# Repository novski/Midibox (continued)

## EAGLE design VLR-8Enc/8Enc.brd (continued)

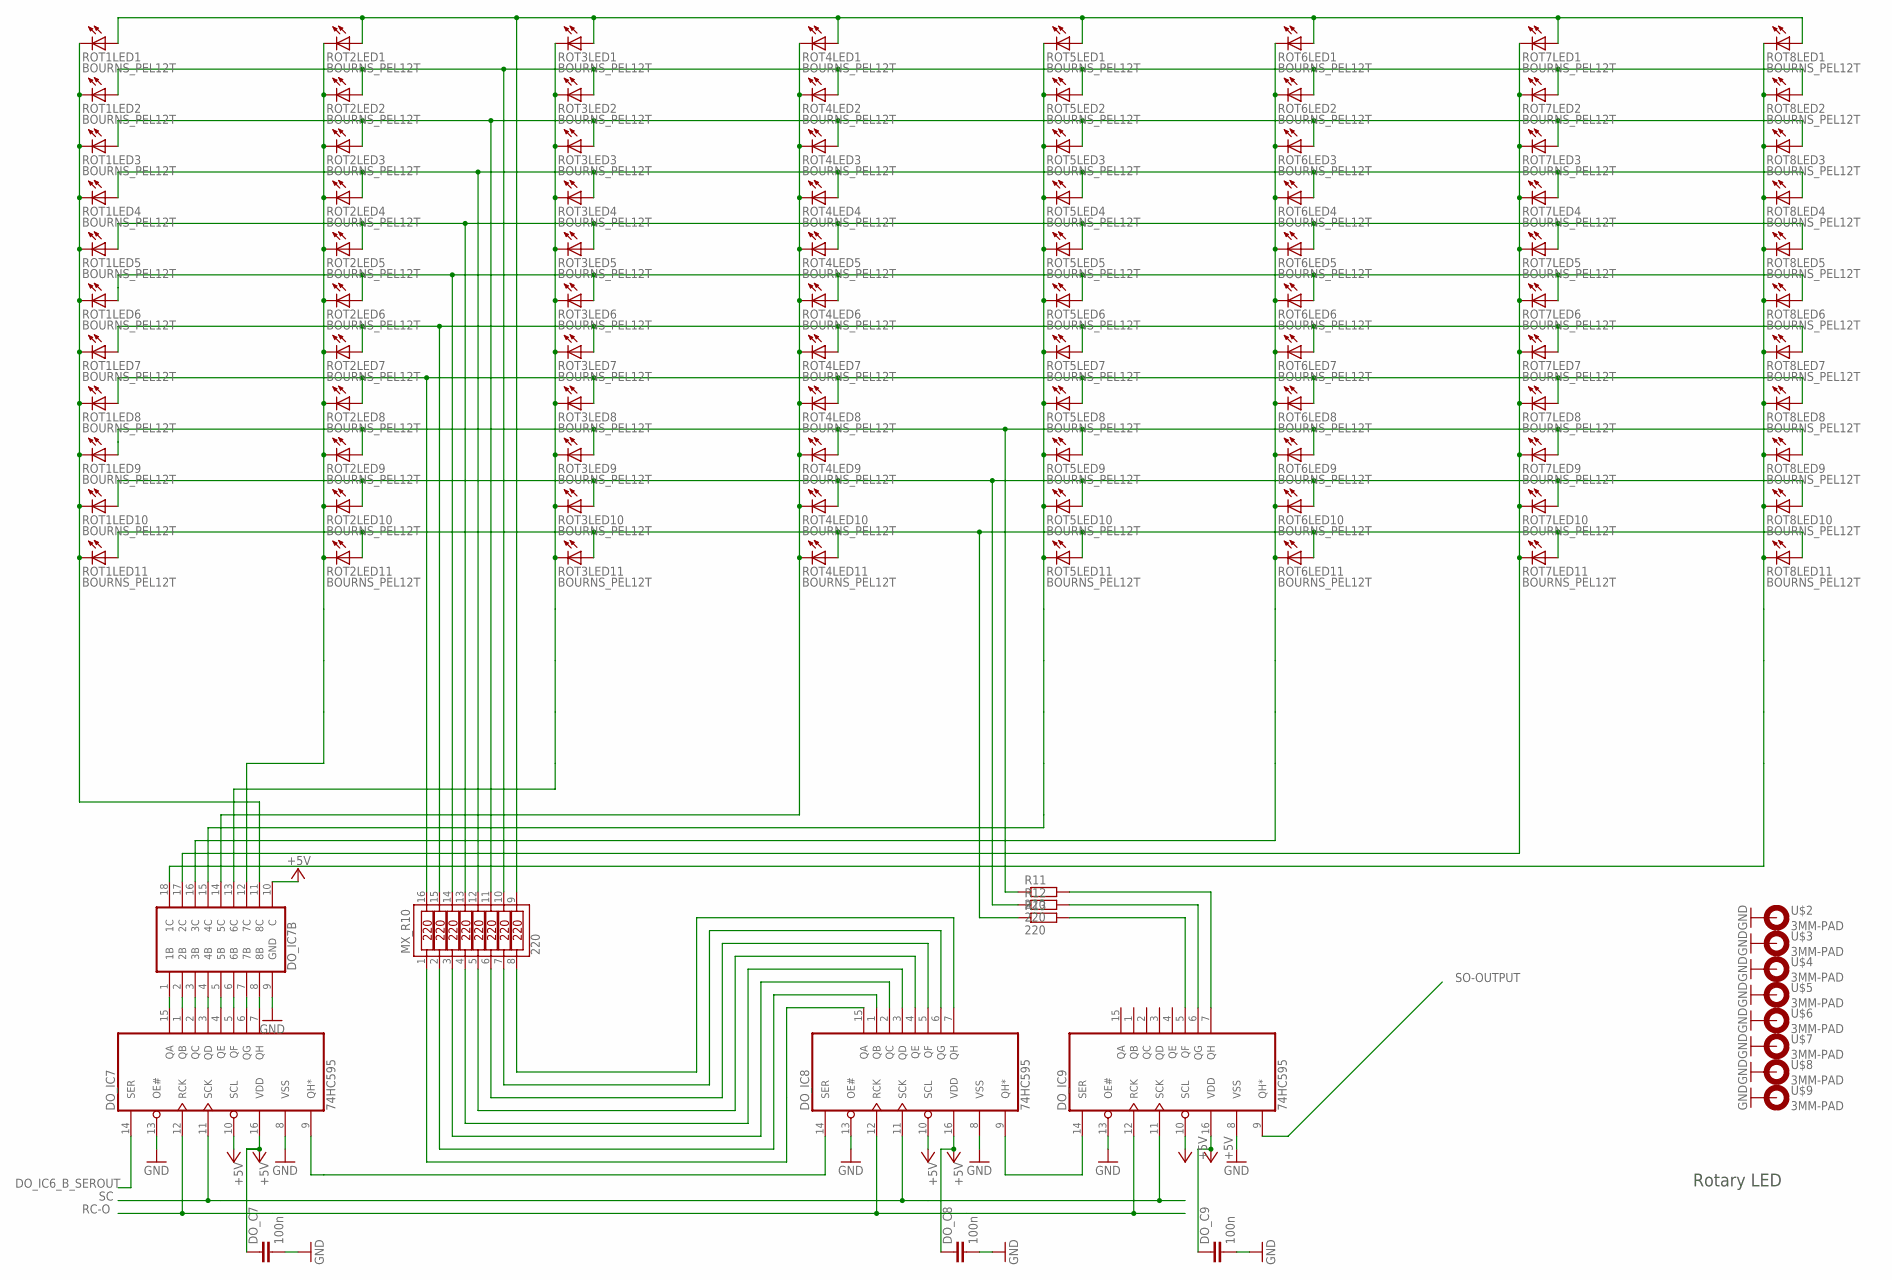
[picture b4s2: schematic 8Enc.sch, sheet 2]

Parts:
DO_C7, DO_C8, DO_C9: 100n; C025-024X044
DO_IC7, DO_IC8, DO_IC9: 74HC595; SO16D
DO_IC7B: ULN2803SO18W; SO18W
MX_R10: 220; SOIC16W
R11, R12, R13: 220; 0204/7
ROT1, ROT2, ROT3, ROT4, ROT5, ROT6, ROT7, ROT8: BOURNS_PEL12T; PEL12T_11-LED-RING
U$2, U$3, U$4, U$5, U$6, U$7, U$8, U$9: 3MM-PAD

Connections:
+5V: DO_C7.1, DO_C8.1, DO_C9.1, DO_IC7.10 (SCL), DO_IC7.16 (VDD), DO_IC7B.10 (C), DO_IC8.10 (SCL), DO_IC8.16 (VDD), DO_IC9.10 (SCL), DO_IC9.16 (VDD); also elsewhere on the board
DO_IC6_B_SEROUT: DO_IC7.14 (SER); also elsewhere on the board
DO_IC7_QA: DO_IC7.15 (QA), DO_IC7B.1 (1B)
DO_IC7_QB: DO_IC7.1 (QB), DO_IC7B.2 (2B)
DO_IC7_QC: DO_IC7.2 (QC), DO_IC7B.3 (3B)
DO_IC7_QD: DO_IC7.3 (QD), DO_IC7B.4 (4B)
DO_IC7_QE: DO_IC7.4 (QE), DO_IC7B.5 (5B)
DO_IC7_QF: DO_IC7.5 (QF), DO_IC7B.6 (6B)
DO_IC7_QG: DO_IC7.6 (QG), DO_IC7B.7 (7B)
DO_IC7_QH: DO_IC7.7 (QH), DO_IC7B.8 (8B)
DO_IC7_SEROUT: DO_IC7.9 (QH*), DO_IC8.14 (SER)
DO_IC8_QA: DO_IC8.15 (QA), MX_R10.1
DO_IC8_QB: DO_IC8.1 (QB), MX_R10.2
DO_IC8_QC: DO_IC8.2 (QC), MX_R10.3
DO_IC8_QD: DO_IC8.3 (QD), MX_R10.4
DO_IC8_QE: DO_IC8.4 (QE), MX_R10.5
DO_IC8_QF: DO_IC8.5 (QF), MX_R10.6
DO_IC8_QG: DO_IC8.6 (QG), MX_R10.7
DO_IC8_QH: DO_IC8.7 (QH), MX_R10.8
DO_IC8_SEROUT: DO_IC8.9 (QH*), DO_IC9.14 (SER)
DO_IC9_QF: DO_IC9.5 (QF), R13.2
DO_IC9_QG: DO_IC9.6 (QG), R12.2
DO_IC9_QH: DO_IC9.7 (QH), R11.2
GND: DO_C7.2, DO_C8.2, DO_C9.2, DO_IC7.8 (VSS), DO_IC7.13 (OE#), DO_IC7B.9 (GND), DO_IC8.8 (VSS), DO_IC8.13 (OE#), DO_IC9.8 (VSS), DO_IC9.13 (OE#), U$2.B3, U$3.B3, U$4.B3, U$5.B3, U$6.B3, U$7.B3, U$8.B3, U$9.B3; also elsewhere on the board
MATRIXLED1: MX_R10.9, ROT1.A1 (A), ROT2.A1 (A), ROT3.A1 (A), ROT4.A1 (A), ROT5.A1 (A), ROT6.A1 (A), ROT7.A1 (A), ROT8.A1 (A)
MATRIXLED2: MX_R10.10, ROT1.A2 (A), ROT2.A2 (A), ROT3.A2 (A), ROT4.A2 (A), ROT5.A2 (A), ROT6.A2 (A), ROT7.A2 (A), ROT8.A2 (A)
MATRIXLED3: MX_R10.11, ROT1.A3 (A), ROT2.A3 (A), ROT3.A3 (A), ROT4.A3 (A), ROT5.A3 (A), ROT6.A3 (A), ROT7.A3 (A), ROT8.A3 (A)
MATRIXLED4: MX_R10.12, ROT1.A4 (A), ROT2.A4 (A), ROT3.A4 (A), ROT4.A4 (A), ROT5.A4 (A), ROT6.A4 (A), ROT7.A4 (A), ROT8.A4 (A)
MATRIXLED5: MX_R10.13, ROT1.A5 (A), ROT2.A5 (A), ROT3.A5 (A), ROT4.A5 (A), ROT5.A5 (A), ROT6.A5 (A), ROT7.A5 (A), ROT8.A5 (A)
MATRIXLED6: MX_R10.14, ROT1.A6 (A), ROT2.A6 (A), ROT3.A6 (A), ROT4.A6 (A), ROT5.A6 (A), ROT6.A6 (A), ROT7.A6 (A), ROT8.A6 (A)
MATRIXLED7: MX_R10.15, ROT1.A7 (A), ROT2.A7 (A), ROT3.A7 (A), ROT4.A7 (A), ROT5.A7 (A), ROT6.A7 (A), ROT7.A7 (A), ROT8.A7 (A)
MATRIXLED8: MX_R10.16, ROT1.A8 (A), ROT2.A8 (A), ROT3.A8 (A), ROT4.A8 (A), ROT5.A8 (A), ROT6.A8 (A), ROT7.A8 (A), ROT8.A8 (A)
MATRIXLED9: R11.1, ROT1.A9 (A), ROT2.A9 (A), ROT3.A9 (A), ROT4.A9 (A), ROT5.A9 (A), ROT6.A9 (A), ROT7.A9 (A), ROT8.A9 (A)
MATRIXLED10: R12.1, ROT1.A10 (A), ROT2.A10 (A), ROT3.A10 (A), ROT4.A10 (A), ROT5.A10 (A), ROT6.A10 (A), ROT7.A10 (A), ROT8.A10 (A)
MATRIXLED11: R13.1, ROT1.A12 (A), ROT2.A12 (A), ROT3.A12 (A), ROT4.A12 (A), ROT5.A12 (A), ROT6.A12 (A), ROT7.A12 (A), ROT8.A12 (A)
MATRIXROT1: DO_IC7B.11 (8C), ROT1.K1 (C), ROT1.K2 (C), ROT1.K3 (C), ROT1.K4 (C), ROT1.K5 (C), ROT1.K6 (C), ROT1.K7 (C), ROT1.K8 (C), ROT1.K9 (C), ROT1.K10 (C), ROT1.K12 (C)
MATRIXROT2: DO_IC7B.12 (7C), ROT2.K1 (C), ROT2.K2 (C), ROT2.K3 (C), ROT2.K4 (C), ROT2.K5 (C), ROT2.K6 (C), ROT2.K7 (C), ROT2.K8 (C), ROT2.K9 (C), ROT2.K10 (C), ROT2.K12 (C)
MATRIXROT3: DO_IC7B.13 (6C), ROT3.K1 (C), ROT3.K2 (C), ROT3.K3 (C), ROT3.K4 (C), ROT3.K5 (C), ROT3.K6 (C), ROT3.K7 (C), ROT3.K8 (C), ROT3.K9 (C), ROT3.K10 (C), ROT3.K12 (C)
MATRIXROT4: DO_IC7B.14 (5C), ROT4.K1 (C), ROT4.K2 (C), ROT4.K3 (C), ROT4.K4 (C), ROT4.K5 (C), ROT4.K6 (C), ROT4.K7 (C), ROT4.K8 (C), ROT4.K9 (C), ROT4.K10 (C), ROT4.K12 (C)
MATRIXROT5: DO_IC7B.15 (4C), ROT5.K1 (C), ROT5.K2 (C), ROT5.K3 (C), ROT5.K4 (C), ROT5.K5 (C), ROT5.K6 (C), ROT5.K7 (C), ROT5.K8 (C), ROT5.K9 (C), ROT5.K10 (C), ROT5.K12 (C)
MATRIXROT6: DO_IC7B.16 (3C), ROT6.K1 (C), ROT6.K2 (C), ROT6.K3 (C), ROT6.K4 (C), ROT6.K5 (C), ROT6.K6 (C), ROT6.K7 (C), ROT6.K8 (C), ROT6.K9 (C), ROT6.K10 (C), ROT6.K12 (C)
MATRIXROT7: DO_IC7B.17 (2C), ROT7.K1 (C), ROT7.K2 (C), ROT7.K3 (C), ROT7.K4 (C), ROT7.K5 (C), ROT7.K6 (C), ROT7.K7 (C), ROT7.K8 (C), ROT7.K9 (C), ROT7.K10 (C), ROT7.K12 (C)
MATRIXROT8: DO_IC7B.18 (1C), ROT8.K1 (C), ROT8.K2 (C), ROT8.K3 (C), ROT8.K4 (C), ROT8.K5 (C), ROT8.K6 (C), ROT8.K7 (C), ROT8.K8 (C), ROT8.K9 (C), ROT8.K10 (C), ROT8.K12 (C)
RC-O: DO_IC7.12 (RCK), DO_IC8.12 (RCK), DO_IC9.12 (RCK); also elsewhere on the board
SC: DO_IC7.11 (SCK), DO_IC8.11 (SCK), DO_IC9.11 (SCK); also elsewhere on the board
SO-OUTPUT: DO_IC9.9 (QH*); also elsewhere on the board

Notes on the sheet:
Rotary LED

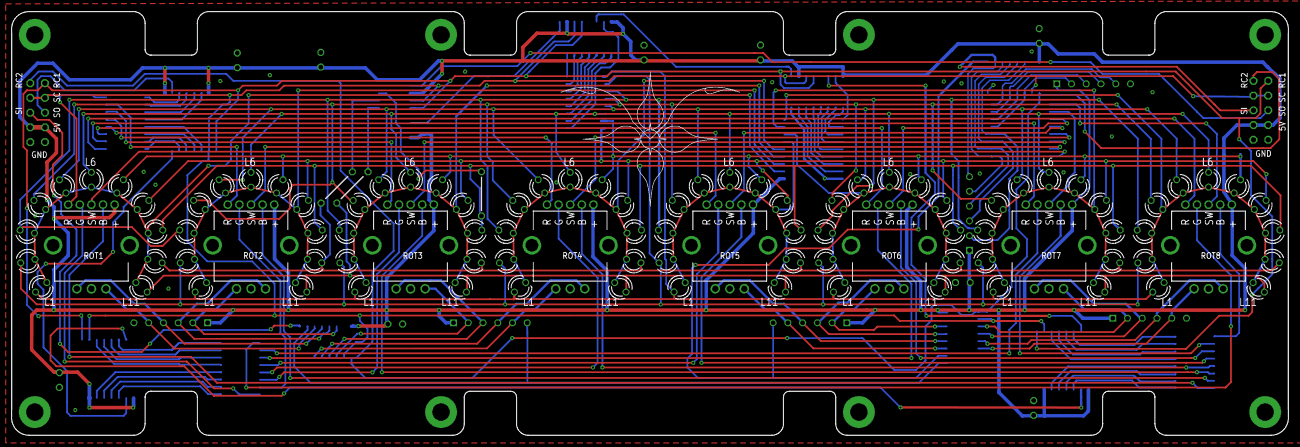
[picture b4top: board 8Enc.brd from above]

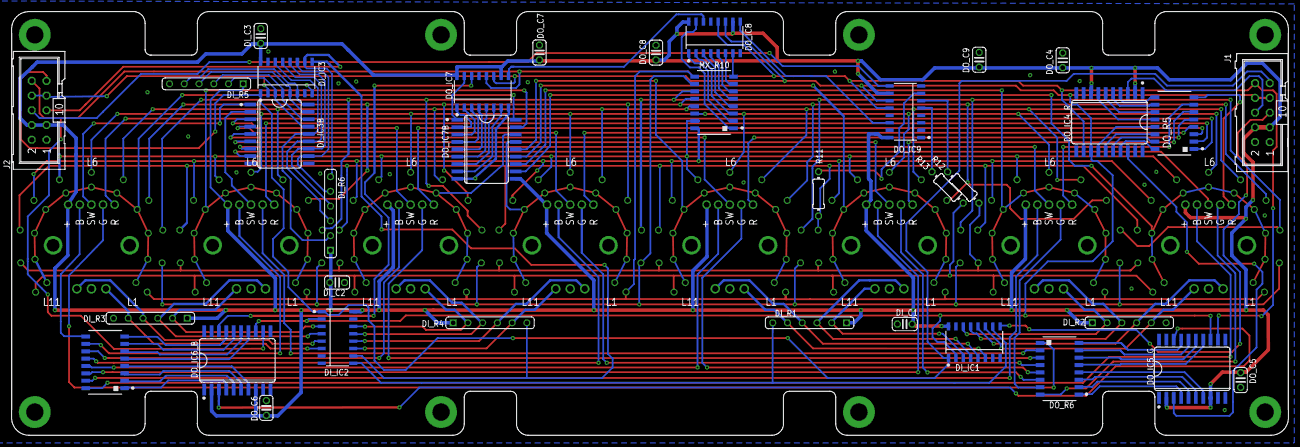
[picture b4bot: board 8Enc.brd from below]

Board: 2 copper layers, 220.0 x 73.0 mm, 56 parts (37 on the bottom side), 134 nets.

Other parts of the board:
U$10, U$13: 8ENC
U$11, U$12, U$14: VLRLAB

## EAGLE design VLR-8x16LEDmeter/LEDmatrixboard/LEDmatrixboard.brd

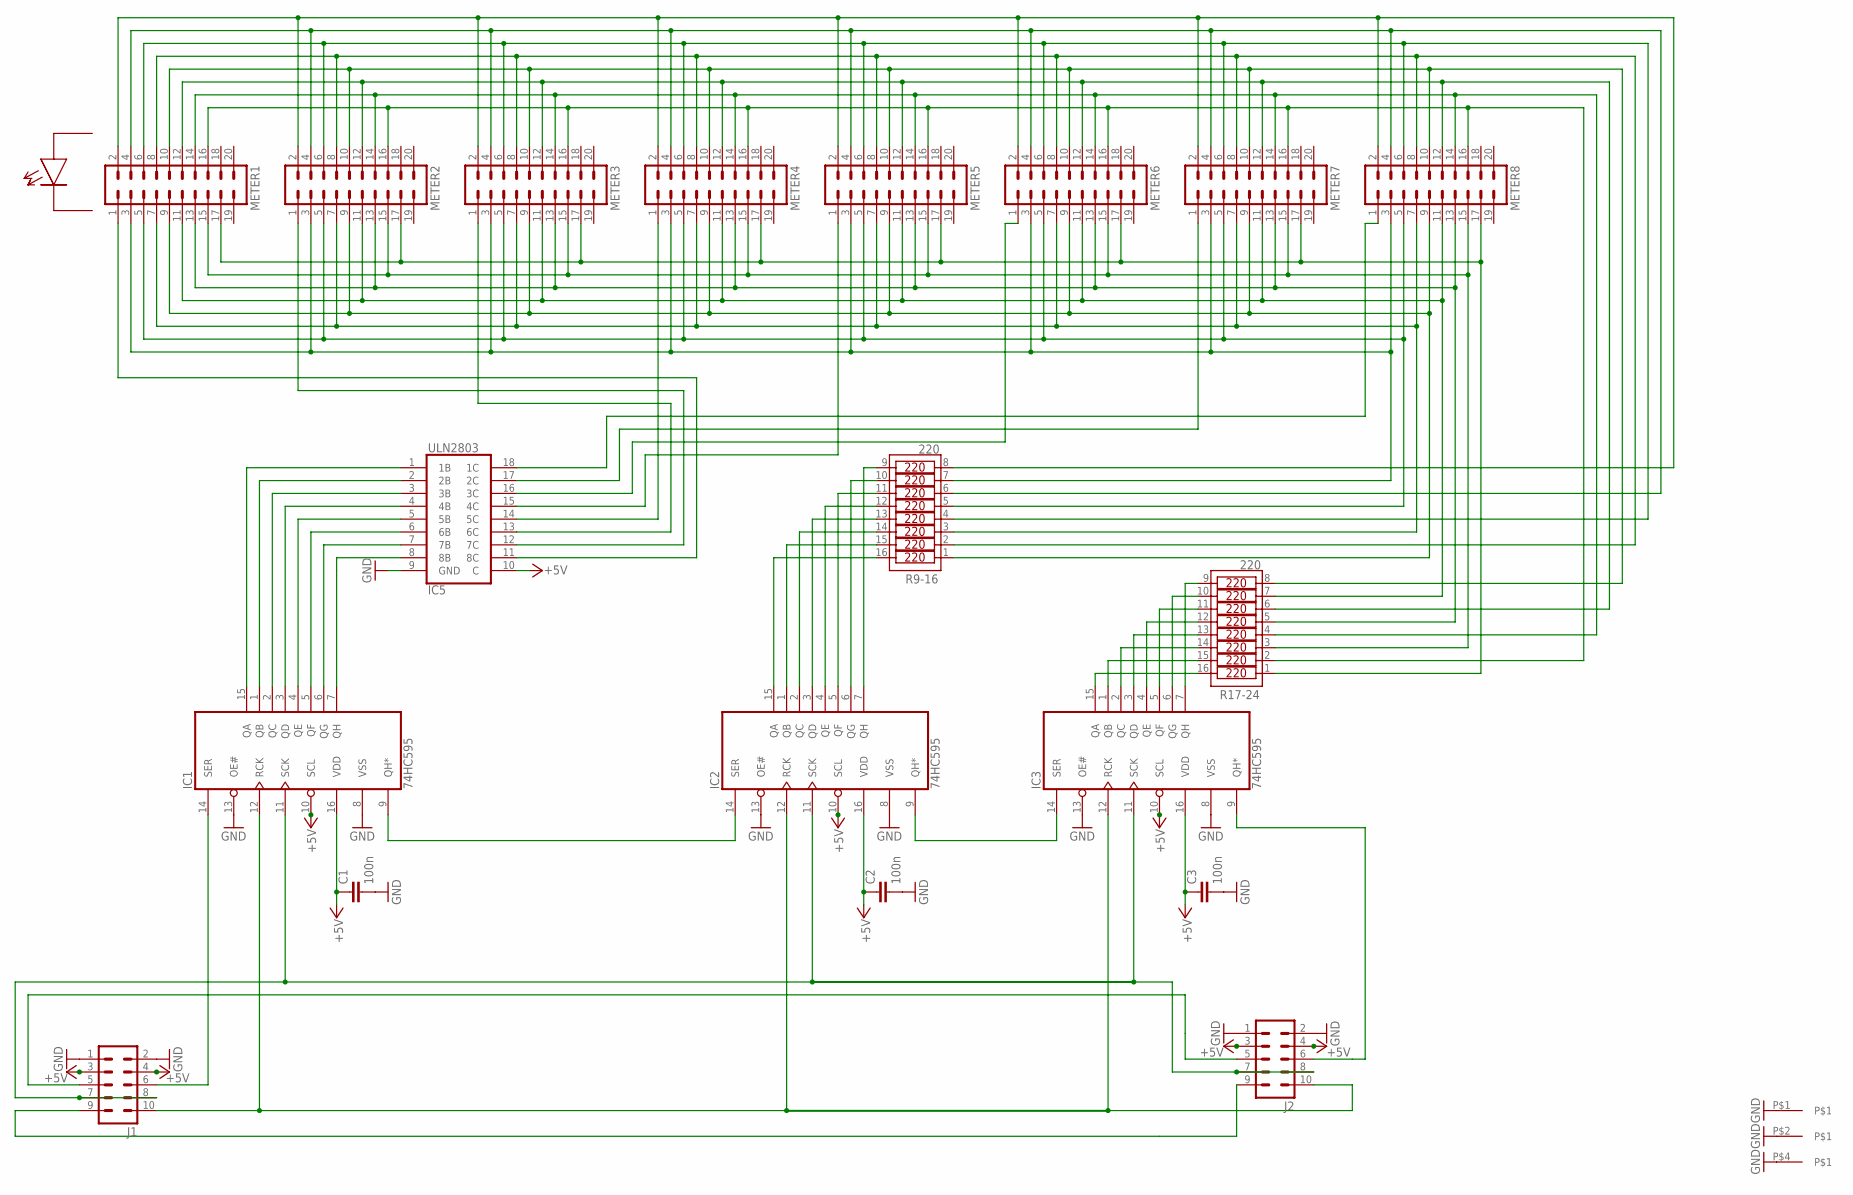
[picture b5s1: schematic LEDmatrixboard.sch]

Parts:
C1, C2, C3: 100n; C025-030X050
IC1, IC2, IC3: 74HC595; SO16D
IC5: ULN2803; SO18W
J1, J2: ML10
METER1, METER2, METER3, METER4, METER5, METER6, METER7, METER8: ML20
R9-16, R17-24: 220; SOIC16W
U$2: MIDIBOX_HALF; MIDIBOX14X6

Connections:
+5V: C1.1, C2.1, C3.1, IC1.10 (SCL), IC1.16 (VDD), IC2.10 (SCL), IC2.16 (VDD), IC3.10 (SCL), IC3.16 (VDD), IC5.10 (C), J1.3, J1.4, J2.3, J2.4
GND: C1.2, C2.2, C3.2, IC1.8 (VSS), IC1.13 (OE#), IC2.8 (VSS), IC2.13 (OE#), IC3.8 (VSS), IC3.13 (OE#), IC5.9 (GND), J1.1, J1.2, J2.1, J2.2, U$2.P$1, U$2.P$2, U$2.P$4
unnamed: IC1.7 (QH), IC5.8 (8B)
unnamed: METER1.2, METER2.2, METER3.2, METER4.2, METER5.2, METER6.2, METER7.2, METER8.2, R9-16.8
unnamed: METER1.3, METER2.3, METER3.3, METER4.3, METER5.3, METER6.3, METER7.3, METER8.3, R9-16.7
unnamed: METER1.4, METER2.4, METER3.4, METER4.4, METER5.4, METER6.4, METER7.4, METER8.4, R9-16.6
unnamed: METER1.5, METER2.5, METER3.5, METER4.5, METER5.5, METER6.5, METER7.5, METER8.5, R9-16.5
unnamed: METER1.6, METER2.6, METER3.6, METER4.6, METER5.6, METER6.6, METER7.6, METER8.6, R9-16.4
unnamed: METER1.7, METER2.7, METER3.7, METER4.7, METER5.7, METER6.7, METER7.7, METER8.7, R9-16.3
unnamed: METER1.8, METER2.8, METER3.8, METER4.8, METER5.8, METER6.8, METER7.8, METER8.8, R9-16.2
unnamed: METER1.9, METER2.9, METER3.9, METER4.9, METER5.9, METER6.9, METER7.9, METER8.9, R9-16.1
unnamed: METER1.10, METER2.10, METER3.10, METER4.10, METER5.10, METER6.10, METER7.10, METER8.10, R17-24.8
unnamed: METER1.11, METER2.11, METER3.11, METER4.11, METER5.11, METER6.11, METER7.11, METER8.11, R17-24.7
unnamed: METER1.12, METER2.12, METER3.12, METER4.12, METER5.12, METER6.12, METER7.12, METER8.12, R17-24.6
unnamed: METER1.13, METER2.13, METER3.13, METER4.13, METER5.13, METER6.13, METER7.13, METER8.13, R17-24.5
unnamed: METER1.14, METER2.14, METER3.14, METER4.14, METER5.14, METER6.14, METER7.14, METER8.14, R17-24.4
unnamed: METER1.15, METER2.15, METER3.15, METER4.15, METER5.15, METER6.15, METER7.15, METER8.15, R17-24.3
unnamed: METER1.16, METER2.16, METER3.16, METER4.16, METER5.16, METER6.16, METER7.16, METER8.16, R17-24.2
unnamed: METER1.17, METER2.17, METER3.17, METER4.17, METER5.17, METER6.17, METER7.17, METER8.17, R17-24.1
unnamed: IC3.15 (QA), R17-24.16
unnamed: IC3.1 (QB), R17-24.15
unnamed: IC3.2 (QC), R17-24.14
unnamed: IC3.3 (QD), R17-24.13
unnamed: IC3.4 (QE), R17-24.12
unnamed: IC3.5 (QF), R17-24.11
unnamed: IC3.6 (QG), R17-24.10
unnamed: IC3.7 (QH), R17-24.9
unnamed: IC2.15 (QA), R9-16.16
unnamed: IC2.1 (QB), R9-16.15
unnamed: IC2.2 (QC), R9-16.14
unnamed: IC2.3 (QD), R9-16.13
unnamed: IC2.4 (QE), R9-16.12
unnamed: IC2.5 (QF), R9-16.11
unnamed: IC2.6 (QG), R9-16.10
unnamed: IC2.7 (QH), R9-16.9
unnamed: IC1.6 (QG), IC5.7 (7B)
unnamed: IC1.5 (QF), IC5.6 (6B)
unnamed: IC1.4 (QE), IC5.5 (5B)
unnamed: IC1.3 (QD), IC5.4 (4B)
unnamed: IC1.2 (QC), IC5.3 (3B)
unnamed: IC1.1 (QB), IC5.2 (2B)
unnamed: IC1.15 (QA), IC5.1 (1B)
unnamed: IC5.11 (8C), METER1.1
unnamed: IC5.12 (7C), METER2.1
unnamed: IC5.13 (6C), METER3.1
unnamed: IC5.14 (5C), METER4.1
unnamed: IC5.15 (4C), METER5.1
unnamed: IC5.16 (3C), METER6.1
unnamed: IC5.17 (2C), METER7.1
unnamed: IC5.18 (1C), METER8.1
unnamed: IC1.9 (QH*), IC2.14 (SER)
unnamed: IC2.9 (QH*), IC3.14 (SER)
unnamed: J1.5, J2.5
unnamed: IC1.14 (SER), J1.6
unnamed: IC3.9 (QH*), J2.6
unnamed: IC1.11 (SCK), IC2.11 (SCK), IC3.11 (SCK), J1.7, J1.8, J2.7, J2.8
unnamed: IC1.12 (RCK), IC2.12 (RCK), IC3.12 (RCK), J1.10, J2.10
unnamed: J1.9, J2.9

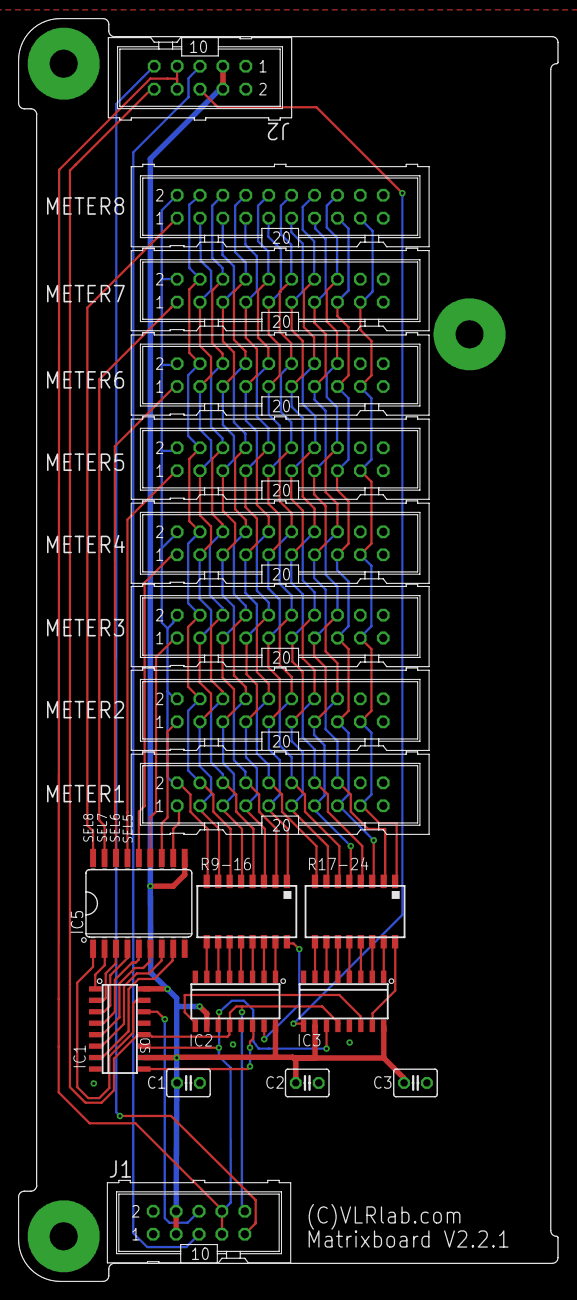
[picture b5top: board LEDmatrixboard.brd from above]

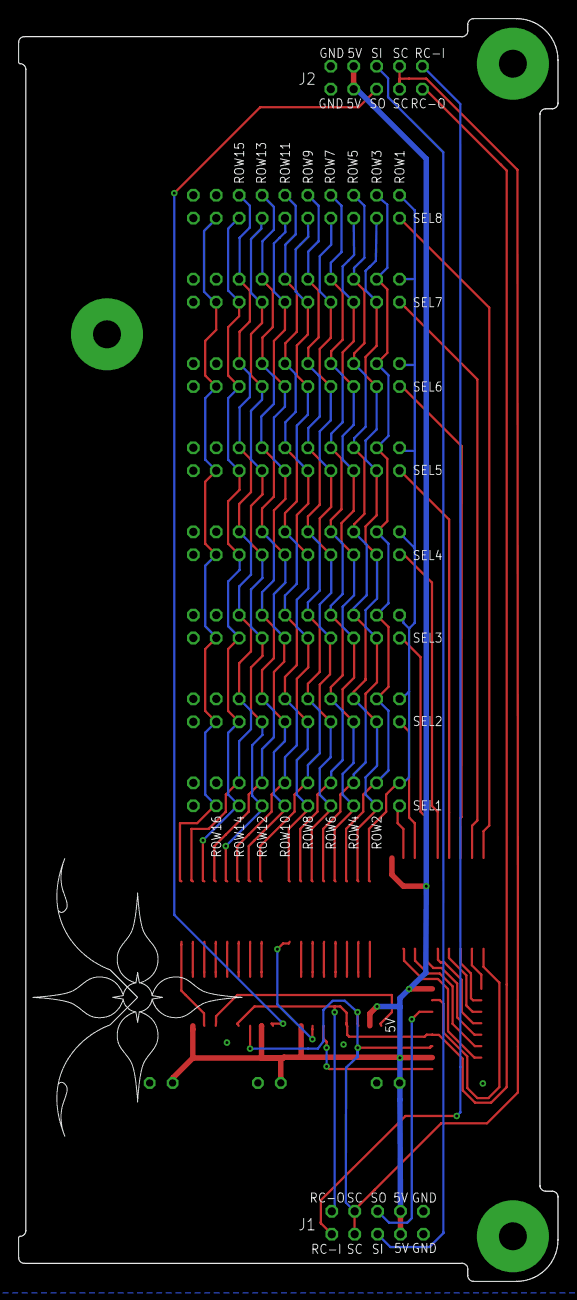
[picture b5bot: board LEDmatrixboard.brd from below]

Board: 2 copper layers, 59.8 x 140.0 mm, 23 parts (2 on the bottom side), 58 nets.

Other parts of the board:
U$3, U$4, U$5: VLRLAB
